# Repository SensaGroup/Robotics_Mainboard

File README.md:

# SENSA - Robotics_Mainboard

SENSA Mainboard is used on the Eurobot 2019 competition.

## Description
The Mainboard is the commander of the robot system. 
We used an Arduino Mega for the base and we developed the extension board

## Features
- 5V/12V inputs with protection
- 4x servo pinouts with external 5V power supply
- 6x 12V pneumatic valve controller
- 2x high-current relays 
- AX-12 support
- 6x optoisolated 12V infrared sensor inputs
- 6x binary 5V sensor inputs
- CAN-Bus (MCP25625)
- NRF24L01
- HC-05 Bluetooth pinout
- I2C/UART pinouts

## Software
All software is written in C for AVR.
View README in the Software folder.

## Pictures

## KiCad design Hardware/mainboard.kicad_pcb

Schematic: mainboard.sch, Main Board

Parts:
C1, C3, C7, C9, C10, C11, C12: 100n; C_0603_1608Metric
C2, C4: 10u; C_0603_1608Metric
C5, C6: 20p; C_0603_1608Metric
C8, C13: CP; CP_Elec_5x5.8
D1, D2, D4: D; D_SMA
D3, D5, D6, D7: LED; LED_0603_1608Metric
J1: Conn_01x10; PinHeader_1x10_P1.27mm_Vertical
J2: AX; JST_XH_B04B-XH-A_1x04_P2.50mm_Vertical
J3: bin_sens1; JST_XH_B03B-XH-A_1x03_P2.50mm_Vertical
J4: bin_sens4; JST_XH_B03B-XH-A_1x03_P2.50mm_Vertical
J5: S1; JST_XH_B02B-XH-A_1x02_P2.50mm_Vertical
J6: bin_sens2; JST_XH_B03B-XH-A_1x03_P2.50mm_Vertical
J7: bin_sens5; JST_XH_B03B-XH-A_1x03_P2.50mm_Vertical
J8: bin_sens3; JST_XH_B03B-XH-A_1x03_P2.50mm_Vertical
J9: bin_sens6; JST_XH_B03B-XH-A_1x03_P2.50mm_Vertical
J10: jump_side; JST_XH_B04B-XH-A_1x04_P2.50mm_Vertical
J11: Senzor1; JST_XH_B03B-XH-A_1x03_P2.50mm_Vertical
J12: tactics_sw; JST_XH_B04B-XH-A_1x04_P2.50mm_Vertical
J13: i2c_con; JST_XH_B04B-XH-A_1x04_P2.50mm_Vertical
J14: ser_con; JST_XH_B03B-XH-A_1x03_P2.50mm_Vertical
J15: CAN; JST_XH_B03B-XH-A_1x03_P2.50mm_Vertical
J17: Senzor3; JST_XH_B03B-XH-A_1x03_P2.50mm_Vertical
J18: Senzor5; JST_XH_B03B-XH-A_1x03_P2.50mm_Vertical
J19: SERVO1; JST_XH_B03B-XH-A_1x03_P2.50mm_Vertical
J20: SERVO2; JST_XH_B03B-XH-A_1x03_P2.50mm_Vertical
J21: S2; JST_XH_B02B-XH-A_1x02_P2.50mm_Vertical
J22: S3; JST_XH_B02B-XH-A_1x02_P2.50mm_Vertical
J23: 12V_IN; PHOENIX_1702473
J24: 5V_IN; PHOENIX_1702473
J25: 5VA_IN; PHOENIX_1702473
J26: S4; JST_XH_B02B-XH-A_1x02_P2.50mm_Vertical
J27: S5; JST_XH_B02B-XH-A_1x02_P2.50mm_Vertical
J28: S6; JST_XH_B02B-XH-A_1x02_P2.50mm_Vertical
J30: Senzor2; JST_XH_B03B-XH-A_1x03_P2.50mm_Vertical
J31: Senzor4; JST_XH_B03B-XH-A_1x03_P2.50mm_Vertical
J32: Senzor6; JST_XH_B03B-XH-A_1x03_P2.50mm_Vertical
J33: SERVO3; JST_XH_B03B-XH-A_1x03_P2.50mm_Vertical
J34: SERVO4; JST_XH_B03B-XH-A_1x03_P2.50mm_Vertical
J35: RELAY2; PHOENIX_1702473
J36: RELAY1; PHOENIX_1702473
K1, K2: G5Q-1A; Relay_SPST_Omron-G5Q-1A
Q1, Q2: DMP2100U; SOT-23
R1, R6, R8, R11, R12, R13, R16, R18, R20, R22, R23, R24: 500; R_0603_1608Metric
R2, R3, R7, R9, R17, R19, R21, R28, R29, R33, R34: 1K; R_0603_1608Metric
R4: 2K; R_0603_1608Metric
R5, R10, R14, R15, R25, R26, R27: 10K; R_0603_1608Metric
R30, R31: 4k7; R_0603_1608Metric
R32: 120; R_0603_1608Metric
RESET1: SW_Push; SW_SPST_FSMSM
U1, U7: ULN2003A; TSSOP-16-1EP_4.4x5mm_P0.65mm
U2, U8, U9, U10, U11, U12: PC817; SOP-4_4.4x2.8mm_P1.27mm
U3: NRF24L01_Breakout; PinHeader_2x04_P2.54mm_Vertical
U4: Bluetooth_HC-05
U5: 74LS241; SOIC-20W_7.5x12.8mm_P1.27mm
U6: MCP25625-x-SS; SSOP-28_5.3x10.2mm_P0.65mm
XA1: Arduino_Mega2560_Shield
Y1: Crystal_GND24; Crystal_SMD_SeikoEpson_FA238V-4Pin_3.2x2.5mm_HandSoldering

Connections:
+3V3: C13.1, U3.2, XA1.3V3 (3.3V); also elsewhere on the board
+5V: C1.1, C2.1, C3.1, C4.1, C7.1, C9.1, C10.1, C11.1, C12.1, J3.1, J4.1, J6.1, J7.1, J8.1, J9.1, J10.1, J12.1, J13.1, Q1.2 (S), R5.1, R29.2, R30.1, R31.1, U2.4, U4.5 (VCC), U5.20 (VCC), U6.1, U6.19, U6.27, U8.4, U9.4, U10.4, U11.4, U12.4, XA1.5V1 (5V), XA1.5V3 (5V), XA1.5V4 (5V); also elsewhere on the board
+5VA: J19.1, J20.1, J33.1, J34.1, Q2.2 (S), R33.2
+12V: D4.1 (K), J5.1, J11.3, J17.3, J18.3, J21.1, J22.1, J26.1, J27.1, J28.1, J30.3, J31.3, J32.3, K1.3, K1.5, K2.3, K2.5, R1.1, R6.1, R8.1, R16.1, R18.1, R20.1, R28.2, U1.9 (COM), U7.9 (COM)
AX_CONTROL: U5.1 (OEa), U5.19 (OEb), XA1.D2 (D2_INT0); also elsewhere on the board
AX_PWR: C8.1, J2.1, J2.2, R34.2
AX_RX: U5.18 (O0a), XA1.D15 (D15_RX3); also elsewhere on the board
AX_SIGNAL: J2.3, U5.2 (I0a), U5.3 (O3b)
AX_TX: U5.17 (I3b), XA1.D14 (D14_TX3); also elsewhere on the board
BIN_SEN1: J3.2, XA1.A0; also elsewhere on the board
BIN_SEN2: J6.2, XA1.A1; also elsewhere on the board
BIN_SEN3: J8.2, XA1.A2; also elsewhere on the board
BIN_SEN4: J4.2, XA1.A3; also elsewhere on the board
BIN_SEN5: J7.2, XA1.A4; also elsewhere on the board
BIN_SEN6: J9.2, XA1.A5; also elsewhere on the board
CAN_CS: U6.17, XA1.D53 (D53_SS); also elsewhere on the board
CAN_INT: U6.13, XA1.D49; also elsewhere on the board
CAN_MISO: U3.7, U6.16, XA1.D50; also elsewhere on the board
CAN_MOSI: U3.6, U6.15, XA1.D51; also elsewhere on the board
CAN_SCK: U3.5, U6.14, XA1.D52; also elsewhere on the board
DBG_RX: U4.3 (TX), XA1.D19 (D19_RX1); also elsewhere on the board
DBG_TX: R3.1, XA1.D18 (D18_TX1); also elsewhere on the board
GND: C1.2, C2.2, C3.2, C4.2, C5.1, C6.1, C7.2, C8.2, C9.2, C10.2, C11.2, C12.2, C13.2, D1.2 (A), D2.2 (A), D3.1 (K), D5.1 (K), D6.1 (K), D7.1 (K), J2.4, J3.3, J4.3, J6.3, J7.3, J8.3, J9.3, J10.4, J11.1, J12.4, J13.4, J14.1, J15.3, J17.1, J18.1, J19.3, J20.3, J23.2, J23.SH1 (SHIELD), J23.SH2 (SHIELD), J24.2, J24.SH1 (SHIELD), J24.SH2 (SHIELD), J25.2, J25.SH1 (SHIELD), J25.SH2 (SHIELD), J30.1, J31.1, J32.1, J33.3, J34.3, J35.1, J35.SH1 (SHIELD), J35.SH2 (SHIELD), J36.1, J36.SH1 (SHIELD), J36.SH2 (SHIELD), Q1.1 (G), Q2.1 (G), R2.1, R4.2, R7.1, R9.1, R10.2, R14.2, R15.2, R17.1, R19.1, R21.1, R25.2, R26.2, R27.2, RESET1.2, U1.8 (GND), U2.2, U3.1, U4.4 (GND), U5.10 (GND), U6.5, U6.10, U6.26, U7.8 (GND), U8.2, U9.2, U10.2, U11.2, U12.2, XA1.GND1 (GND), XA1.GND2 (GND), XA1.GND3 (GND), XA1.GND5 (GND), XA1.GND6 (GND); also elsewhere on the board
JUMPER: J10.2, XA1.D3 (D3_INT1); also elsewhere on the board
NRF_CE: U3.3, XA1.D47; also elsewhere on the board
NRF_CS: U3.4, XA1.D48; also elsewhere on the board
unnamed: C5.2, U6.8, Y1.1
unnamed: C6.2, U6.9, Y1.3
unnamed: D1.1 (K), J36.2, K1.2
unnamed: D2.1 (K), J35.2, K2.2
unnamed: D3.2 (A), R28.1
unnamed: D4.2 (A), J23.1
unnamed: D5.2 (A), R29.1
unnamed: D6.2 (A), R33.1
unnamed: D7.2 (A), R34.1
unnamed 35: J1.1, XA1.A15; also elsewhere on the board
unnamed 36: J1.2, XA1.A14; also elsewhere on the board
unnamed 37: J1.3, XA1.A13; also elsewhere on the board
unnamed 38: J1.4, XA1.A12; also elsewhere on the board
unnamed 39: J1.5, XA1.A11; also elsewhere on the board
unnamed 40: J1.6, XA1.A10; also elsewhere on the board
unnamed 41: J1.7, XA1.A9; also elsewhere on the board
unnamed 42: J1.8, XA1.A8; also elsewhere on the board
unnamed 43: J1.9, XA1.A7; also elsewhere on the board
unnamed 44: J1.10, XA1.A6; also elsewhere on the board
unnamed: J11.2, R1.2, R2.2, R13.1
unnamed: J15.1, R32.2, U6.4
unnamed: J15.2, R32.1, U6.3
unnamed: J17.2, R6.2, R7.2, R11.1
unnamed: J18.2, R8.2, R9.2, R12.1
unnamed: J24.1, Q1.3 (D)
unnamed: J25.1, Q2.3 (D)
unnamed: J30.2, R16.2, R17.2, R22.1
unnamed: J31.2, R18.2, R19.2, R23.1
unnamed: J32.2, R20.2, R21.2, R24.1
unnamed: R3.2, R4.1, U4.2 (RX)
unnamed: R5.2, U6.7
unnamed: R11.2, U8.1
unnamed: R12.2, U9.1
unnamed: R13.2, U2.1
unnamed: R22.2, U10.1
unnamed: R23.2, U11.1
unnamed: R24.2, U12.1
unnamed: U6.20, U6.24
unnamed: U6.21, U6.28
unnamed 93: XA1.AREF; also elsewhere on the board
unnamed 94: XA1.D0 (D0_RX0); also elsewhere on the board
unnamed 95: XA1.D1 (D1_TX0); also elsewhere on the board
unnamed 96: XA1.D7; also elsewhere on the board
unnamed 97: XA1.D22; also elsewhere on the board
unnamed 98: XA1.D24; also elsewhere on the board
unnamed 99: XA1.D25; also elsewhere on the board
unnamed 100: XA1.D26; also elsewhere on the board
unnamed 101: XA1.D27; also elsewhere on the board
unnamed 102: XA1.D28; also elsewhere on the board
unnamed 103: XA1.D30; also elsewhere on the board
unnamed 104: XA1.D38; also elsewhere on the board
unnamed 105: XA1.D39; also elsewhere on the board
unnamed 106: XA1.D40; also elsewhere on the board
unnamed 107: XA1.D42; also elsewhere on the board
unnamed 108: XA1.D44; also elsewhere on the board
unnamed 109: XA1.D46; also elsewhere on the board
unnamed 110: XA1.IORF (IOREF); also elsewhere on the board
unnamed 111: XA1.SCL; also elsewhere on the board
unnamed 112: XA1.SDA; also elsewhere on the board
unnamed 113: XA1.VIN; also elsewhere on the board
PWM1: J19.2, XA1.D10; also elsewhere on the board
PWM2: J20.2, XA1.D11; also elsewhere on the board
PWM3: J33.2, XA1.D12; also elsewhere on the board
PWM4: J34.2, XA1.D13; also elsewhere on the board
R1_CONT: U1.1 (I1), U1.2 (I2), XA1.D8; also elsewhere on the board
R1_SIG: K1.1, U1.15 (O2), U1.16 (O1)
R2_CONT: U1.3 (I3), U1.4 (I4), XA1.D9; also elsewhere on the board
R2_SIG: K2.1, U1.13 (O4), U1.14 (O3)
RST: RESET1.1, U6.18, XA1.RST1 (RESET); also elsewhere on the board
SCL: J13.2, R31.2, XA1.D21 (D21_SCL); also elsewhere on the board
SDA: J13.3, R30.2, XA1.D20 (D20_SDA); also elsewhere on the board
SENSOR1: R10.1, U2.3, XA1.D45; also elsewhere on the board
SENSOR2: R25.1, U10.3, XA1.D43; also elsewhere on the board
SENSOR3: R14.1, U8.3, XA1.D41; also elsewhere on the board
SENSOR4: R26.1, U11.3, XA1.D37; also elsewhere on the board
SENSOR5: R15.1, U9.3, XA1.D29; also elsewhere on the board
SENSOR6: R27.1, U12.3, XA1.D23; also elsewhere on the board
SER_RX: J14.2, XA1.D17 (D17_RX2); also elsewhere on the board
SER_TX: J14.3, XA1.D16 (D16_TX2); also elsewhere on the board
SIDE: J10.3, XA1.D4; also elsewhere on the board
TACTIC1: J12.3, XA1.D5; also elsewhere on the board
TACTIC2: J12.2, XA1.D6; also elsewhere on the board
_S1: J5.2, U7.16 (O1)
_S1_SIG: U7.1 (I1), XA1.D36; also elsewhere on the board
_S2: J21.2, U7.15 (O2)
_S2_SIG: U7.2 (I2), XA1.D34; also elsewhere on the board
_S3: J22.2, U7.14 (O3)
_S3_SIG: U7.3 (I3), XA1.D35; also elsewhere on the board
_S4: J26.2, U7.13 (O4)
_S4_SIG: U7.4 (I4), XA1.D33; also elsewhere on the board
_S5: J27.2, U7.12 (O5)
_S5_SIG: U7.5 (I5), XA1.D32; also elsewhere on the board
_S6: J28.2, U7.11 (O6)
_S6_SIG: U7.6 (I6), XA1.D31; also elsewhere on the board

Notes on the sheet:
Control a low-current device (ON/OFF) (electric valve)
12V, 5VA, 5V Inputs with protection, LED indicators
MCP25625 - CAN controller CAN 2.0 supported, up to 1Mbps Working on 16MHz
Arduino MEGA pinout
AX-12 servo support
HC-05 Bluetooth module
nRF24L01
fit if necessary
6x 12V sensors with isolation (PC817)
Two high power relays (12V devices)
4x servo
6x binary 5V switch connectors
Jumper, Side & Tactics connector Communication connectors (I2C, Serial)

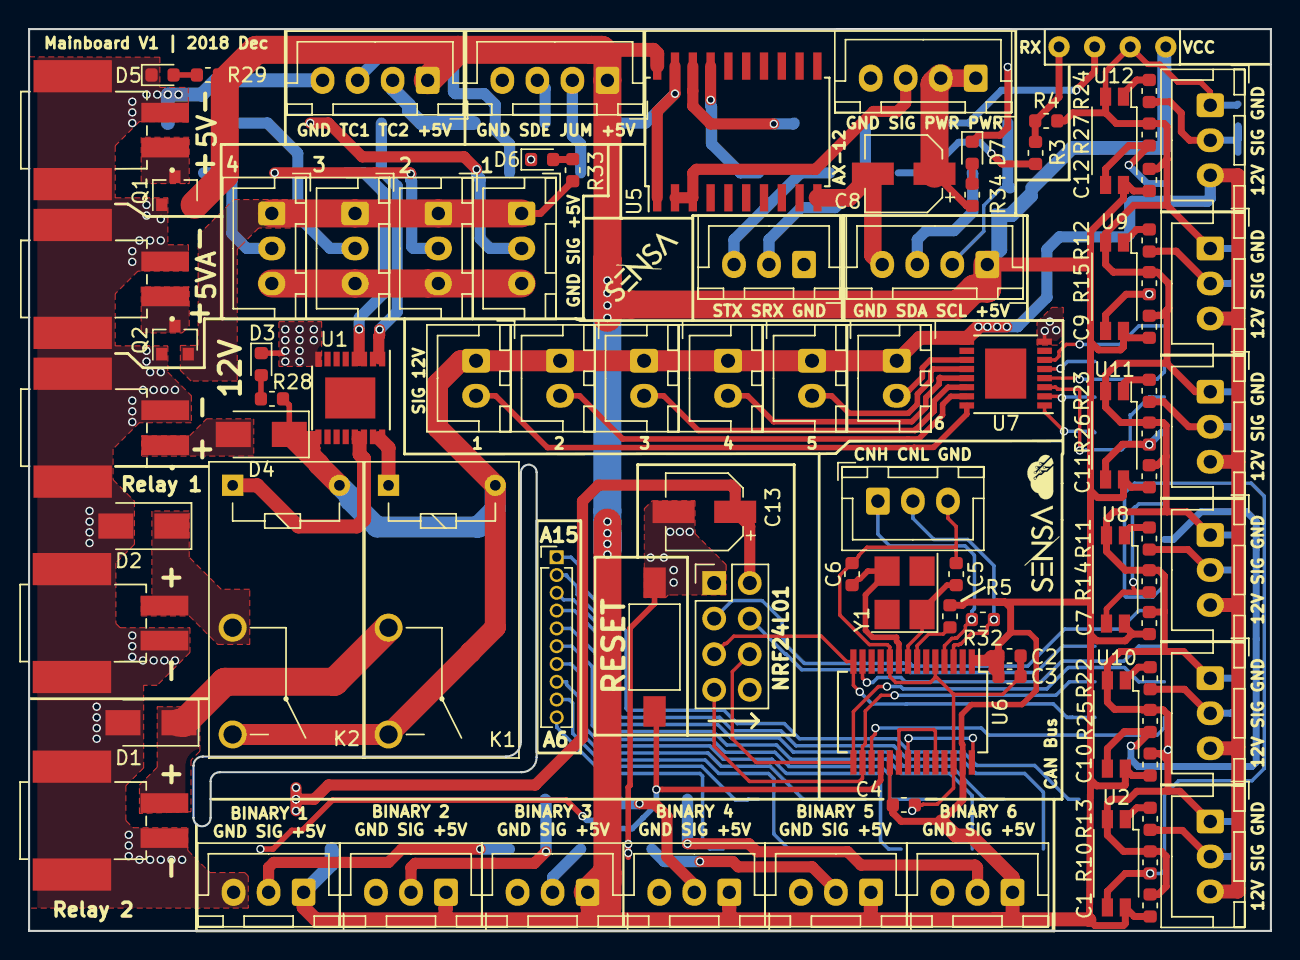
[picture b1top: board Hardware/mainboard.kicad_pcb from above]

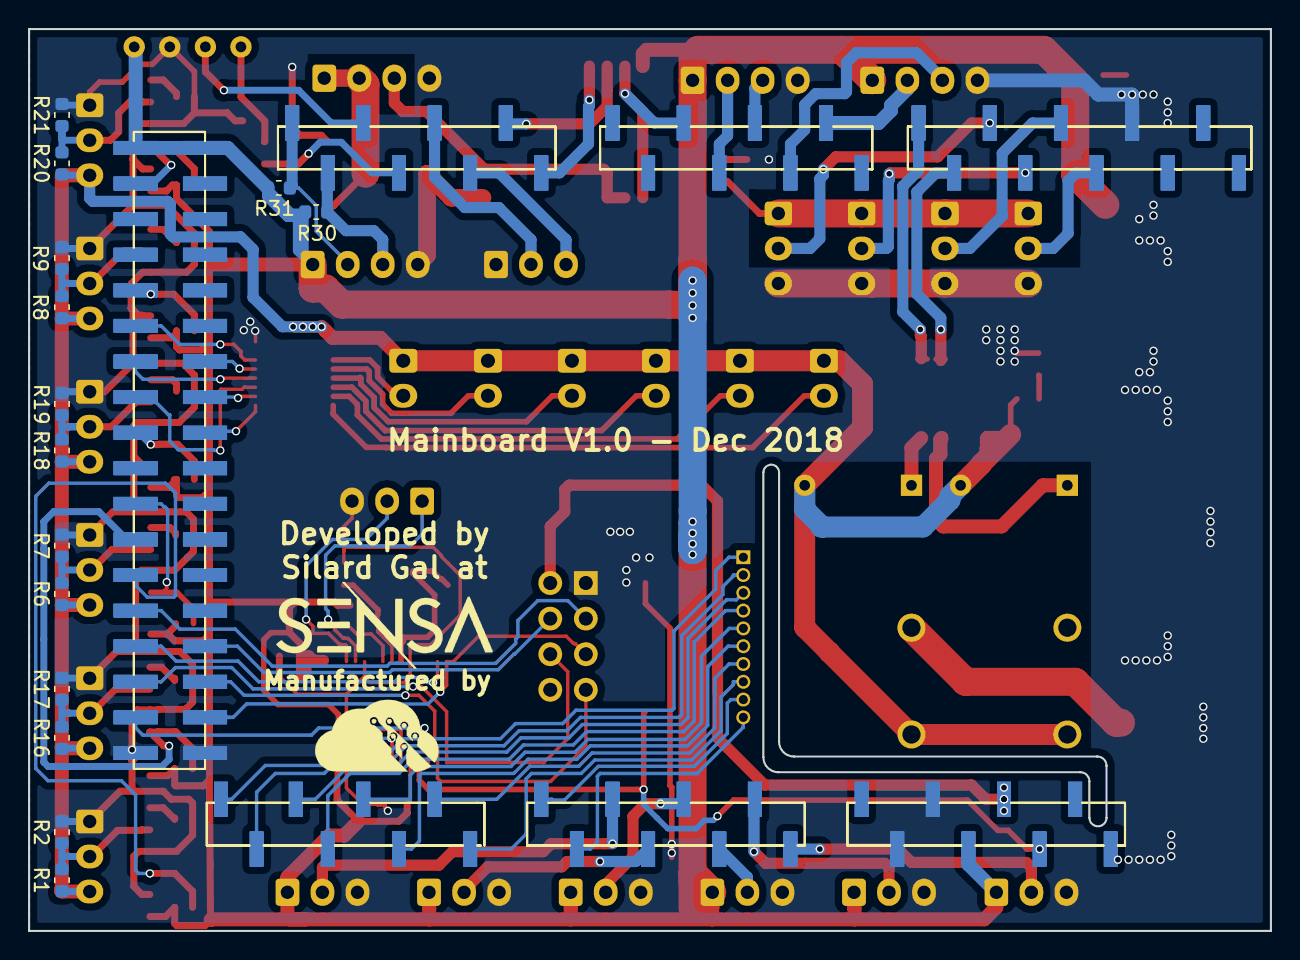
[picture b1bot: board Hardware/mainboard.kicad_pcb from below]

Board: 2 copper layers, 88.6 x 64.4 mm, 108 parts (14 on the bottom side), 120 nets.

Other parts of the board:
XA1#2: Arduino_Mega2560_Shield

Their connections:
+3V3: XA1#2.3V3; also elsewhere on the board
+5V: XA1#2.5V1, XA1#2.5V3, XA1#2.5V4; also elsewhere on the board
AX_CONTROL: XA1#2.D2; also elsewhere on the board
AX_RX: XA1#2.D15; also elsewhere on the board
AX_TX: XA1#2.D14; also elsewhere on the board
BIN_SEN1: XA1#2.A0; also elsewhere on the board
BIN_SEN2: XA1#2.A1; also elsewhere on the board
BIN_SEN3: XA1#2.A2; also elsewhere on the board
BIN_SEN4: XA1#2.A3; also elsewhere on the board
BIN_SEN5: XA1#2.A4; also elsewhere on the board
BIN_SEN6: XA1#2.A5; also elsewhere on the board
CAN_CS: XA1#2.D53; also elsewhere on the board
CAN_INT: XA1#2.D49; also elsewhere on the board
CAN_MISO: XA1#2.D50; also elsewhere on the board
CAN_MOSI: XA1#2.D51; also elsewhere on the board
CAN_SCK: XA1#2.D52; also elsewhere on the board
DBG_RX: XA1#2.D19; also elsewhere on the board
DBG_TX: XA1#2.D18; also elsewhere on the board
GND: XA1#2.GND1, XA1#2.GND2, XA1#2.GND3, XA1#2.GND5, XA1#2.GND6; also elsewhere on the board
JUMPER: XA1#2.D3; also elsewhere on the board
NRF_CE: XA1#2.D47; also elsewhere on the board
NRF_CS: XA1#2.D48; also elsewhere on the board
unnamed 35: XA1#2.A15; also elsewhere on the board
unnamed 36: XA1#2.A14; also elsewhere on the board
unnamed 37: XA1#2.A13; also elsewhere on the board
unnamed 38: XA1#2.A12; also elsewhere on the board
unnamed 39: XA1#2.A11; also elsewhere on the board
unnamed 40: XA1#2.A10; also elsewhere on the board
unnamed 41: XA1#2.A9; also elsewhere on the board
unnamed 42: XA1#2.A8; also elsewhere on the board
unnamed 43: XA1#2.A7; also elsewhere on the board
unnamed 44: XA1#2.A6; also elsewhere on the board
unnamed 93: XA1#2.AREF; also elsewhere on the board
unnamed 94: XA1#2.D0; also elsewhere on the board
unnamed 95: XA1#2.D1; also elsewhere on the board
unnamed 96: XA1#2.D7; also elsewhere on the board
unnamed 97: XA1#2.D22; also elsewhere on the board
unnamed 98: XA1#2.D24; also elsewhere on the board
unnamed 99: XA1#2.D25; also elsewhere on the board
unnamed 100: XA1#2.D26; also elsewhere on the board
unnamed 101: XA1#2.D27; also elsewhere on the board
unnamed 102: XA1#2.D28; also elsewhere on the board
unnamed 103: XA1#2.D30; also elsewhere on the board
unnamed 104: XA1#2.D38; also elsewhere on the board
unnamed 105: XA1#2.D39; also elsewhere on the board
unnamed 106: XA1#2.D40; also elsewhere on the board
unnamed 107: XA1#2.D42; also elsewhere on the board
unnamed 108: XA1#2.D44; also elsewhere on the board
unnamed 109: XA1#2.D46; also elsewhere on the board
unnamed 110: XA1#2.IORF; also elsewhere on the board
unnamed 111: XA1#2.SCL; also elsewhere on the board
unnamed 112: XA1#2.SDA; also elsewhere on the board
unnamed 113: XA1#2.VIN; also elsewhere on the board
PWM1: XA1#2.D10; also elsewhere on the board
PWM2: XA1#2.D11; also elsewhere on the board
PWM3: XA1#2.D12; also elsewhere on the board
PWM4: XA1#2.D13; also elsewhere on the board
R1_CONT: XA1#2.D8; also elsewhere on the board
R2_CONT: XA1#2.D9; also elsewhere on the board
RST: XA1#2.RST1; also elsewhere on the board
SCL: XA1#2.D21; also elsewhere on the board
SDA: XA1#2.D20; also elsewhere on the board
SENSOR1: XA1#2.D45; also elsewhere on the board
SENSOR2: XA1#2.D43; also elsewhere on the board
SENSOR3: XA1#2.D41; also elsewhere on the board
SENSOR4: XA1#2.D37; also elsewhere on the board
SENSOR5: XA1#2.D29; also elsewhere on the board
SENSOR6: XA1#2.D23; also elsewhere on the board
SER_RX: XA1#2.D17; also elsewhere on the board
SER_TX: XA1#2.D16; also elsewhere on the board
SIDE: XA1#2.D4; also elsewhere on the board
TACTIC1: XA1#2.D5; also elsewhere on the board
TACTIC2: XA1#2.D6; also elsewhere on the board
_S1_SIG: XA1#2.D36; also elsewhere on the board
_S2_SIG: XA1#2.D34; also elsewhere on the board
_S3_SIG: XA1#2.D35; also elsewhere on the board
_S4_SIG: XA1#2.D33; also elsewhere on the board
_S5_SIG: XA1#2.D32; also elsewhere on the board
_S6_SIG: XA1#2.D31; also elsewhere on the board

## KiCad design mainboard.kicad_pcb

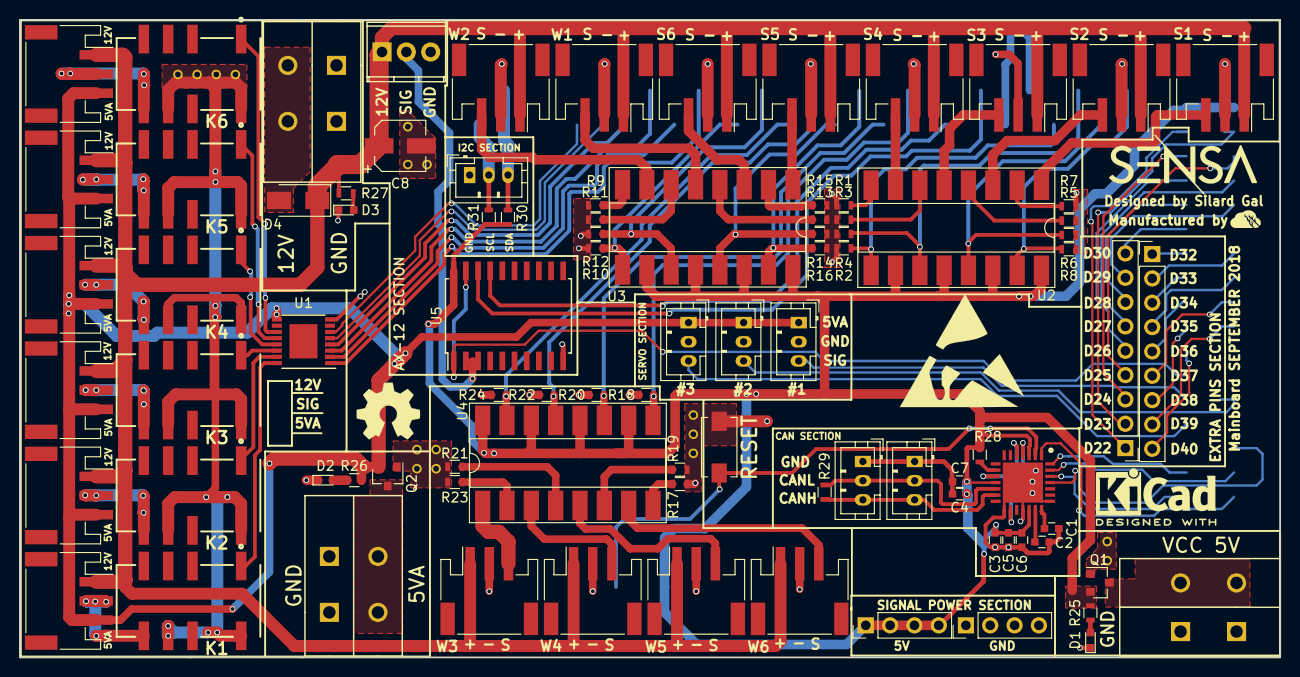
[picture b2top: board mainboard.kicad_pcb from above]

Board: 2 copper layers, 131.6 x 66.5 mm, 92 parts (1 on the bottom side), 106 nets.

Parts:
C1, C2: C; C_0603
C3: 10u; C_0603
C4, C5, C6, C7: 0.1u; C_0603
C8: CP; CP_Elec_5x5.8
D1, D2, D3: LED; LED_0603
D4: D; D_SMA
IC1: MCP25625-E_ML; QFN65P600X600X100-29N-D
J1: SENS1; JST_PH_S3B-PH-SM4-TB_03x2.00mm_Angled
J2: SENS2; JST_PH_S3B-PH-SM4-TB_03x2.00mm_Angled
J3: SENS3; JST_PH_S3B-PH-SM4-TB_03x2.00mm_Angled
J4: SENS4; JST_PH_S3B-PH-SM4-TB_03x2.00mm_Angled
J5: SENS5; JST_PH_S3B-PH-SM4-TB_03x2.00mm_Angled
J6: SENS6; JST_PH_S3B-PH-SM4-TB_03x2.00mm_Angled
J7: R1; JST_PH_S3B-PH-SM4-TB_03x2.00mm_Angled
J8: R2; JST_PH_S3B-PH-SM4-TB_03x2.00mm_Angled
J9: R3; JST_PH_S3B-PH-SM4-TB_03x2.00mm_Angled
J10: R4; JST_PH_S3B-PH-SM4-TB_03x2.00mm_Angled
J11: R5; JST_PH_S3B-PH-SM4-TB_03x2.00mm_Angled
J12: R6; JST_PH_S3B-PH-SM4-TB_03x2.00mm_Angled
J13: SW1; JST_PH_S3B-PH-SM4-TB_03x2.00mm_Angled
J14: SW2; JST_PH_S3B-PH-SM4-TB_03x2.00mm_Angled
J15: SW3; JST_PH_S3B-PH-SM4-TB_03x2.00mm_Angled
J16: SW4; JST_PH_S3B-PH-SM4-TB_03x2.00mm_Angled
J17: SW5; JST_PH_S3B-PH-SM4-TB_03x2.00mm_Angled
J18: SW6; JST_PH_S3B-PH-SM4-TB_03x2.00mm_Angled
J19, J20, J21, J22, J26, J27: Conn_01x03; JST_PH_B3B-PH-K_03x2.00mm_Straight
J23, J24, J25: Screw_Terminal_01x02; ZFKDS
J28, J31: Conn_01x04; Pin_Header_Straight_1x04_Pitch2.54mm
J29: Conn_01x03; GS3
J30: Screw_Terminal_01x03; TerminalBlock_Phoenix_MPT-2.54mm_3pol
J32, J33: Conn_01x10; Pin_Header_Straight_1x09_Pitch2.54mm
K1, K2, K3, K4, K5, K6: EE2-5NU
Q1, Q2: DMP2100U; SOT-23
R1, R3, R5, R7, R9, R11, R13, R15, R17, R19, R21, R23, R25, R26: 330; R_0603
R2, R4, R6, R8, R10, R12, R14, R16, R18, R20, R22, R24, R30, R31: 4k7; R_0603
R27: 1K; R_0603
R28: 10k; R_0603
R29: 120; R_0603
SW1: SW_Push; SW_SPST_EVQPE1
U1: ULN2003A; TSSOP-16-1EP_4.4x5mm_Pitch0.65mm
U2, U3, U4: LTV-847; DIP-16_W8.89mm_SMDSocket_LongPads
U5: 74LS241; SOIC-20W_7.5x12.8mm_Pitch1.27mm
XA1: Arduino_Mega2560_Shield

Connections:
+5V: C3.1, C4.1, C5.1, C6.1, C7.1, IC1.3, IC1.11, IC1.19, J28.1, J28.2, J28.3, J28.4, Q1.2, R25.1, R28.2, R30.1, R31.1, U2.10, U2.12, U2.14, U2.16, U3.10, U3.12, U3.14, U3.16, U4.10, U4.12, U4.14, U4.16, U5.20, XA1.5V1, XA1.5V3, XA1.5V4
+5VA: J7.3, J8.3, J9.3, J10.3, J11.3, J12.3, J19.1, J20.1, J21.1, Q2.2, R26.1, U1.9
+12V: C8.1, D4.1, J1.1, J2.1, J3.1, J4.1, J5.1, J6.1, J7.1, J8.1, J9.1, J10.1, J11.1, J12.1, J13.1, J14.1, J15.1, J16.1, J17.1, J18.1, J30.1, R27.1
AX_CONTROL: U5.1, U5.19, XA1.D42
AX_RX: U5.18, XA1.D15
AX_SIGNAL: J30.2, U5.2, U5.3
AX_TX: U5.17, XA1.D14
CANH: IC1.13, J26.3, J27.3, R29.1
CANL: IC1.12, J26.2, J27.2, R29.2
CAN_CS: IC1.1, XA1.D53
CAN_INT: IC1.25, XA1.D49
CAN_MISO: IC1.28, XA1.D50
CAN_MOSI: IC1.27, XA1.D51
CAN_SCK: IC1.26, XA1.D52
C_RX: IC1.5, IC1.10
C_TX: IC1.4, IC1.16
DBG_RX: J29.3, XA1.D17
DBG_TX: J29.2, XA1.D16
GND: C1.2, C2.2, C3.2, C4.2, C5.2, C6.2, C7.2, C8.2, D1.1, D2.1, D3.1, IC1.15, IC1.18, IC1.22, IC1.29, J1.2, J2.2, J3.2, J4.2, J5.2, J6.2, J13.2, J14.2, J15.2, J16.2, J17.2, J18.2, J19.2, J20.2, J21.2, J22.1, J23.1, J24.1, J25.1, J26.1, J27.1, J29.1, J30.3, J31.1, J31.2, J31.3, J31.4, K1.6, K1.8, K2.6, K2.8, K3.6, K3.8, K4.6, K4.8, K5.6, K5.8, K6.6, K6.8, Q1.1, Q2.1, R1.1, R2.2, R3.1, R4.2, R5.1, R6.2, R7.1, R8.2, R9.1, R10.2, R11.1, R12.2, R13.1, R14.2, R15.1, R16.2, R17.1, R18.2, R19.1, R20.2, R21.1, R22.2, R23.1, R24.2, SW1.2, U1.8, U5.10, XA1.GND1, XA1.GND2, XA1.GND3, XA1.GND5, XA1.GND6
unnamed: C1.1, IC1.21
unnamed: C2.1, IC1.20
unnamed: D1.2, R25.2
unnamed: D2.2, R26.2
unnamed: D3.2, R27.2
unnamed: D4.2, J25.2
unnamed: IC1.9, R28.1
unnamed: J23.2, Q1.3
unnamed: J24.2, Q2.3
unnamed: J32.1, XA1.D22
unnamed: J32.2, XA1.D23
unnamed: J32.3, XA1.D24
unnamed: J32.4, XA1.D25
unnamed: J32.5, XA1.D26
unnamed: J32.6, XA1.D27
unnamed: J32.7, XA1.D28
unnamed: J32.8, XA1.D29
unnamed: J32.9, XA1.D30
unnamed: J33.1, XA1.D32
unnamed: J33.2, XA1.D33
unnamed: J33.3, XA1.D34
unnamed: J33.4, XA1.D35
unnamed: J33.5, XA1.D36
unnamed: J33.6, XA1.D37
unnamed: J33.7, XA1.D38
unnamed: J33.8, XA1.D39
unnamed: J33.9, XA1.D40
unnamed: R1.2, U2.8
unnamed: R3.2, U2.6
unnamed: R5.2, U2.4
unnamed: R7.2, U2.2
unnamed: R9.2, U3.8
unnamed: R11.2, U3.6
unnamed: R13.2, U3.4
unnamed: R15.2, U3.2
unnamed: R17.2, U4.8
unnamed: R19.2, U4.6
unnamed: R21.2, U4.4
unnamed: R23.2, U4.2
PWM1: J19.3, XA1.D44
PWM2: J20.3, XA1.D45
PWM3: J21.3, XA1.D46
R1: J7.2, K1.5
R1_CONT: U1.1, XA1.D8
R1_SIG: K1.1, U1.16
R2: J8.2, K2.5
R2_CONT: U1.2, XA1.D9
R2_SIG: K2.1, U1.15
R3: J9.2, K3.5
R3_CONT: U1.3, XA1.D10
R3_SIG: K3.1, U1.14
R4: J10.2, K4.5
R4_CONT: U1.4, XA1.D11
R4_SIG: K4.1, U1.13
R5: J11.2, K5.5
R5_CONT: U1.5, XA1.D12
R5_SIG: K5.1, U1.12
R6: J12.2, K6.5
R6_CONT: U1.6, XA1.D13
R6_SIG: K6.1, U1.11
RST: IC1.2, SW1.1, XA1.RST1
SCL: J22.2, R31.2, XA1.SCL
SDA: J22.3, R30.2, XA1.SDA
SENS1: J1.3, U2.1
SENS2: J2.3, U2.3
SENS3: J3.3, U2.5
SENS4: J4.3, U2.7
SENS5: J5.3, U3.1
SENS6: J6.3, U3.3
SO_1: R8.1, U2.15, XA1.D21
SO_2: R6.1, U2.13, XA1.D20
SO_3: R4.1, U2.11, XA1.D19
SO_4: R2.1, U2.9, XA1.D18
SO_5: R16.1, U3.15, XA1.D2
SO_6: R14.1, U3.13, XA1.D3
SW1: J13.3, U3.5
SW2: J14.3, U3.7
SW3: J15.3, U4.1
SW4: J16.3, U4.3
SW5: J17.3, U4.5
SW6: J18.3, U4.7
SWO_1: R12.1, U3.11, XA1.D6
SWO_2: R10.1, U3.9, XA1.D7
SWO_3: R24.1, U4.15, XA1.D5
SWO_4: R22.1, U4.13, XA1.D4
SWO_5: R20.1, U4.11, XA1.D1
SWO_6: R18.1, U4.9, XA1.D0

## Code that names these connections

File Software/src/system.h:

#ifndef SYSTEM_H
#define SYSTEM_H

#include <Arduino.h>
#include "actuator.h"
#include "TimerThree.h" 
#include "nrf.h"
#include "can.h"
#include "odometry.h"
#include "mechanism.h"
#include "detection.h"

#define PIN_JUMPER  3
#define PIN_TACTIC1 5
#define PIN_TACTIC2 6
#define PIN_SIDE    4

void init_system(void);
void set_match_started(void);
unsigned long get_sys_time(void);

int get_tactic1(void);
int get_tactic2(void);
int get_side(void);

struct goto_fields
{
	struct odometry_position goto_position;
	uint8_t speed;
	uint8_t direction;
	uint8_t	(*callback)();
	uint8_t (*callback_end)();
};


#endif

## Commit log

2018-08-30 Beta version
2019-01-04 Finished version 1.0
2019-03-26 Readme and images
2019-03-26 Added images
2019-03-28 Hardware/Software folders
2019-03-28 Force push
2019-03-28 Deleted...
2019-03-28 Fxied readme
2019-03-28 Added comments to lidar and sys
2019-03-28 Comments to actuator
2019-03-28 Added comments to can
2019-03-28 gotos fancy comments
2019-03-28 added comments to odometry
2019-03-28 positions comments
2019-03-30 Mechanisms, actuators, lidar and nrf sa;; seti[
2019-04-04 "update"
